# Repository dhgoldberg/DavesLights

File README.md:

DavesLights
===========

The RGB LED display I've put up in our livingroom.

In progress...

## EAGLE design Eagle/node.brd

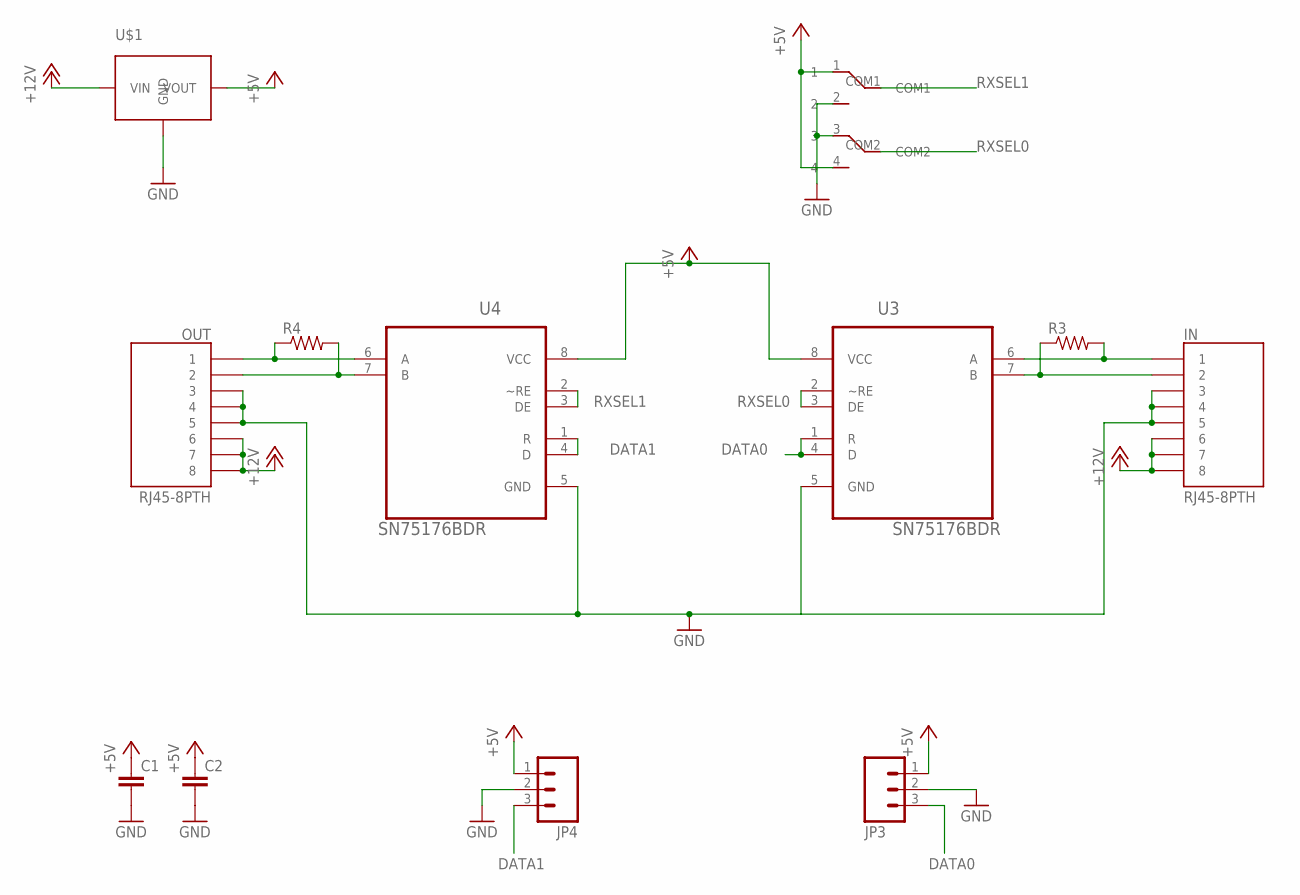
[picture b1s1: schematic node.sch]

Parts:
C1, C2: CAPPTH1; CAP-PTH-5MM
IN: RJ45-8PTH; RJ45-8
JP3, JP4: M03JST-PTH; JST-3-PTH
OUT: RJ45-8PTH; RJ45-8
R3, R4: RESISTORPTH-1/2W; AXIAL-0.5
U3, U4: SN75176BDR; SOIC127P600X175-8N
U$1: TSR1-2450; TSR-1
U$2: SWITCH-NKK-DPDT

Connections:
+5V: C1.1, C2.1, JP3.1, JP4.1, U3.8 (VCC), U4.8 (VCC), U$1.3 (VOUT), U$2.1, U$2.4
+12V: IN.6, IN.7, IN.8, OUT.6, OUT.7, OUT.8, U$1.1 (VIN)
DATA0: JP3.3, U3.1 (R), U3.4 (D)
DATA1: JP4.3, U4.1 (R), U4.4 (D)
GND: C1.2, C2.2, IN.3, IN.4, IN.5, JP3.2, JP4.2, OUT.3, OUT.4, OUT.5, U3.5 (GND), U4.5 (GND), U$1.2 (GND), U$2.2, U$2.3
unnamed: IN.1, R3.P$2 (2), U3.6 (A)
unnamed: IN.2, R3.P$1 (1), U3.7 (B)
unnamed: OUT.1, R4.P$1 (1), U4.6 (A)
unnamed: OUT.2, R4.P$2 (2), U4.7 (B)
RXSEL0: U3.2 (~RE), U3.3 (DE), U$2.COM2
RXSEL1: U4.2 (~RE), U4.3 (DE), U$2.COM1

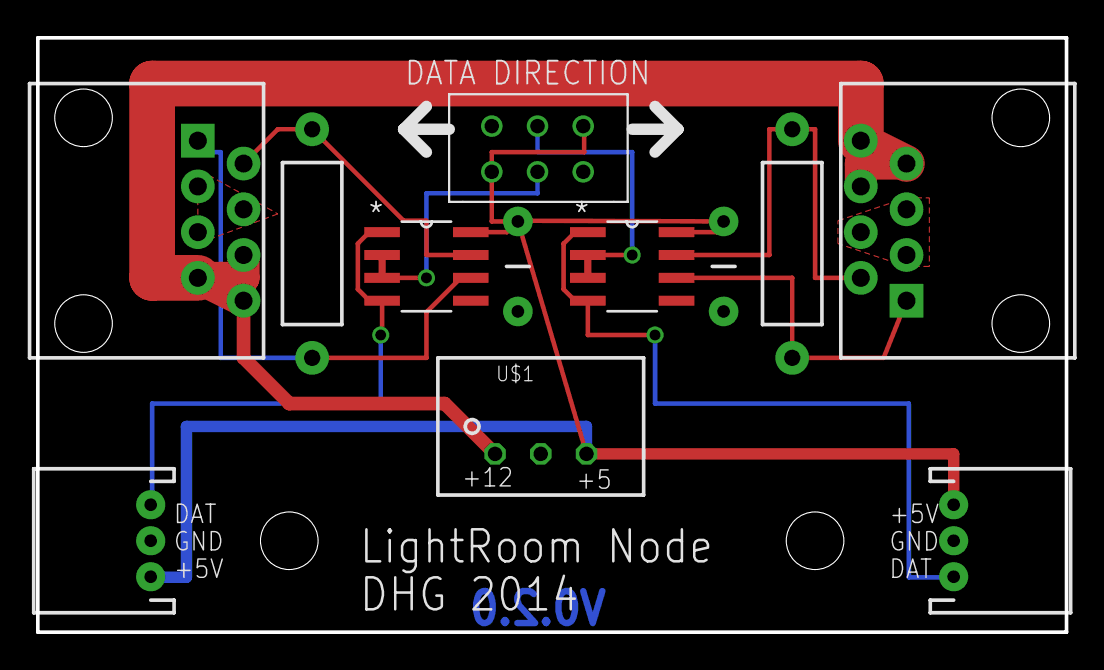
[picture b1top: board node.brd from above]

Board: 2 copper layers, 57.1 x 33.0 mm, 12 parts (0 on the bottom side), 11 nets.

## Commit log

2014-10-16 :neckbeard: Added .gitattributes & .gitignore files
2014-11-01 Improving CO color cycling
    Improving algo to cycle colors associated with frequencies when the bass
    bucket peaks.
2014-11-09 Improving color picking
    adding CIE1931 correction to fixed color mode. closes #2
2014-11-09 Display color picker on load
    Display color picker on load if fixed color mode is enabled. Fixes #4

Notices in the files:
parts and their libraries:
SparkFun-Connectors: Licensing: CC v3.0 Share-Alike You are welcome to use this library for commercial purposes.
